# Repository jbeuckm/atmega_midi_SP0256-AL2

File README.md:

Try this SYSEX Editor app: [https://midi-tts.herokuapp.com/editor/index.html](https://midi-tts.herokuapp.com/editor/index.html)

Accepts MIDI signals to control a speech synthesizer IC. LTC6904 (on a DIP adapter) controls the clock frequency of the SP chip.

## MIDI Sysex Messages

Function   | Start | Prefix       | Message | End
-----------|-------|--------------|---------|-------
Set Channel| F0    | 77 34 01 00  | cc | f7
Speak Word | F0    | 77 34 01 01  | a1 a2 a3 ... (allophones) | f7
Assign Note On Word | F0    | 77 34 01 02 | nn (note #) a1 a2 a3 ... (allophones) | f7
Assign Note Off Word| F0    | 77 34 01 03 | nn (note #) a1 a2 a3 ... (allophones) | f7
Clock Freq | F0    | 77 34 01 40  | 0\[bits 13-7\] 0\[bits 6-0\] (khz) | f7
Save Config| F0    | 77 34 01 70  | (none) | f7
Load Config| F0    | 77 34 01 71  | (none) | f7
Dump Request| F0    | 77 34 01 72  | (none) | f7
Sysex Dump | F0    | 77 34 01 73  | (assignment data) | f7

After words have been assigned to keys, the device operates as a monophonic synthesizer, playing the word assigned to a key when that key is pressed.

If a "speak word" message is received while a key is down, the word is assigned to that key.

MIDI notes on the base channel trigger words that have been assigned to those keys.

MIDI notes on the base channel + 1 set the pitch by altering the clock frequency of the speech chip.

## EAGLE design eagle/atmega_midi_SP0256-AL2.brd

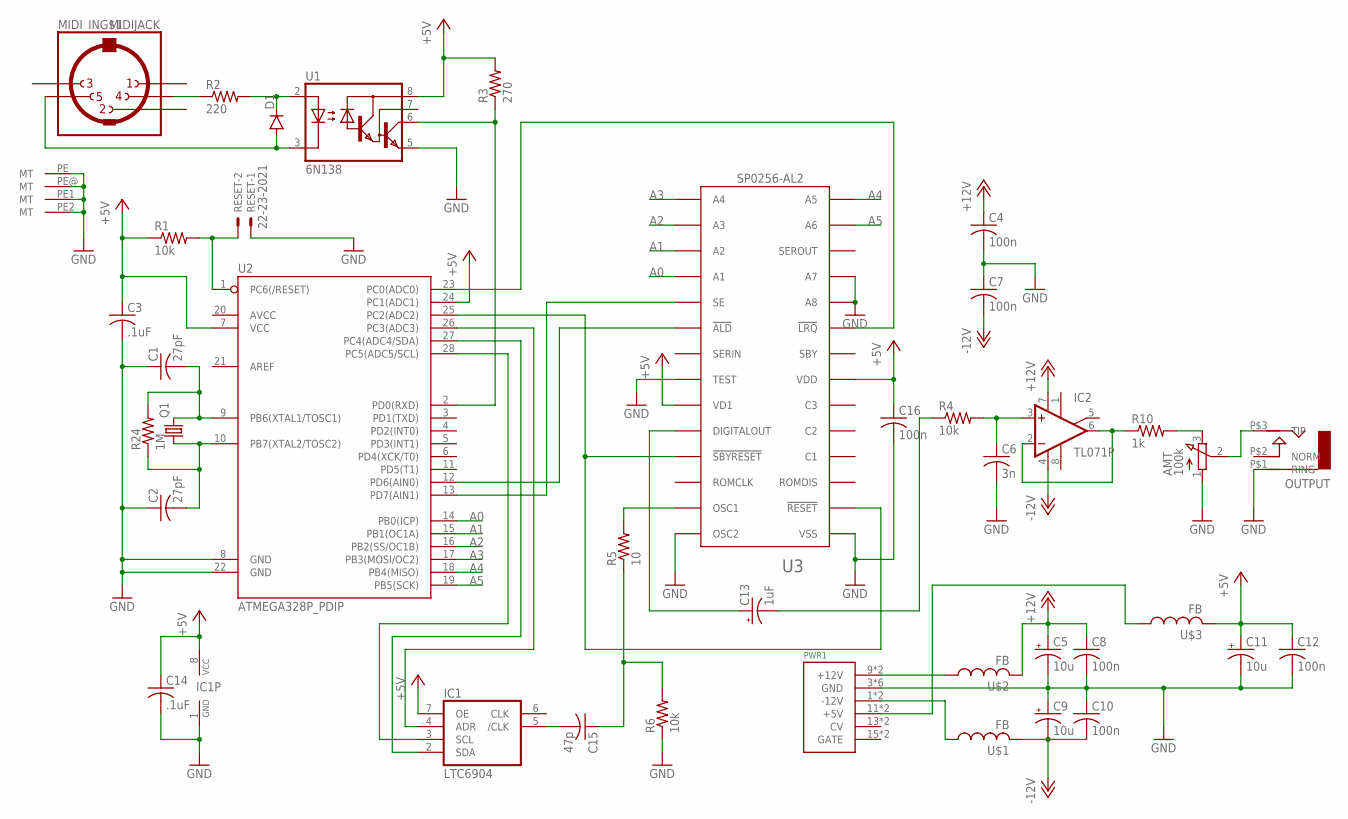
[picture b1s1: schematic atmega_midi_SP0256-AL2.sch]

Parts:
AMT: 100k; 3RP/1610N
C1, C2: 27pF; C025-040X050
C3, C14: .1uF; C025-030X050
C4: 100n; C050-024X044
C5, C9, C11: 10u; B45181A
C6: 3n; C050-024X044
C7, C8, C10, C12, C16: 100n; C025-030X050
C13: 1uF; E15-6
C15: 47p; C050-024X044
D1: DIODE1N4148; DIODE-1N4148
IC1: LTC6904; DIL08
IC2: TL071P; DIL08
MIDI_IN: MIDIJACK; CP-2350
OUTPUT: AUDIO-JACK; ERTHENVAR-JACK-90DEG
PWR1: POWER; POWER_16
Q1: CRYSTALHC49S; HC49/S
R1, R4, R6: 10k; 0207/7
R2: 220; 0207/7
R3: 270; 0207/7
R5: 10; 0207/7
R10: 1k; 0207/7
R24: 1M; 0207/7
RESET: 22-23-2021
U1: 6N138; DIL08
U2: ATMEGA328P_PDIP; DIL28-3
U3: SP0256-AL2; DIL28-6
U$1, U$2, U$3: FB

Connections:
+5V: C3.1, C11.+, C12.1, C14.1, C16.1, IC1.7 (OE), IC1.8 (VCC), R1.1, R3.2, U1.8 (VCC), U2.7 (VCC), U2.24 (PC1(ADC1)), U3.P$7 (VDD), U3.P$23 (VD1), U$3.P$2 (2)
+12V: C4.1, C5.+, C8.1, IC2.7 (V+), U$2.P$2 (2)
-12V: C7.2, C9.-, C10.2, IC2.4 (V-), U$1.P$2 (2)
A0: U2.14 (PB0(ICP)), U3.P$18 (A1)
A1: U2.15 (PB1(OC1A)), U3.P$17 (A2)
A2: U2.16 (PB2(SS/OC1B)), U3.P$16 (A3)
A3: U2.17 (PB3(MOSI/OC2)), U3.P$15 (A4)
A4: U2.18 (PB4(MISO)), U3.P$14 (A5)
A5: U2.19 (PB5(SCK)), U3.P$13 (A6)
GND: AMT.1 (A), C1.1, C2.1, C3.2, C4.2, C5.-, C6.2, C7.1, C8.2, C9.+, C10.1, C11.-, C12.2, C14.2, C16.2, IC1.1 (GND), MIDI_IN.PE (MT), MIDI_IN.PE1 (MT), MIDI_IN.PE2 (MT), MIDI_IN.PE@ (MT), OUTPUT.P$1 (RING), PWR1.3 (GND), PWR1.4 (GND), PWR1.5 (GND), PWR1.6 (GND), PWR1.7 (GND), PWR1.8 (GND), R6.1, RESET.1, U1.5 (GND), U2.8 (GND), U2.22 (GND), U3.P$1 (VSS), U3.P$10 (A8), U3.P$11 (A7), U3.P$22 (TEST), U3.P$28 (OSC2)
unnamed: U2.25 (PC2(ADC2)), U3.P$2 (!RESET), U3.P$25 (!SBYRESET)
unnamed: PWR1.11 (+5V), PWR1.12 (+5V), U$3.P$1 (1)
unnamed: D1.A, MIDI_IN.5, U1.3 (C)
unnamed: C1.2, Q1.2, R24.2, U2.9 (PB6(XTAL1/TOSC1))
unnamed: C2.2, Q1.1, R24.1, U2.10 (PB7(XTAL2/TOSC2))
unnamed: C6.1, IC2.3 (+IN), R4.2
unnamed: D1.C, R2.2, U1.2 (A)
unnamed: MIDI_IN.4, R2.1
unnamed: AMT.3 (E), R10.2
unnamed: U2.12 (PD6(AIN0)), U3.P$20 (!ALD)
unnamed: PWR1.9 (+12V), PWR1.10 (+12V), U$2.P$1 (1)
unnamed: IC2.2 (-IN), IC2.6 (OUT), R10.1
unnamed: AMT.2 (S), OUTPUT.P$3 (TIP)
unnamed: PWR1.1 (-12V), PWR1.2 (-12V), U$1.P$1 (1)
unnamed: IC1.3 (SCL), U2.28 (PC5(ADC5/SCL))
unnamed: U2.13 (PD7(AIN1)), U3.P$19 (SE)
unnamed: C13.+, U3.P$24 (DIGITALOUT)
unnamed: IC1.2 (SDA), U2.27 (PC4(ADC4/SDA))
unnamed: IC1.4 (ADR), U2.26 (PC3(ADC3))
unnamed: U2.23 (PC0(ADC0)), U3.P$9 (!LRQ)
unnamed: C15.2, IC1.5 (/CLK)
unnamed: R3.1, U1.6 (VO), U2.2 (PD0(RXD))
unnamed: C13.-, R4.1
unnamed: R5.2, U3.P$27 (OSC1)
unnamed: C15.1, R5.1, R6.2
unnamed: R1.2, RESET.2, U2.1 (PC6(/RESET))

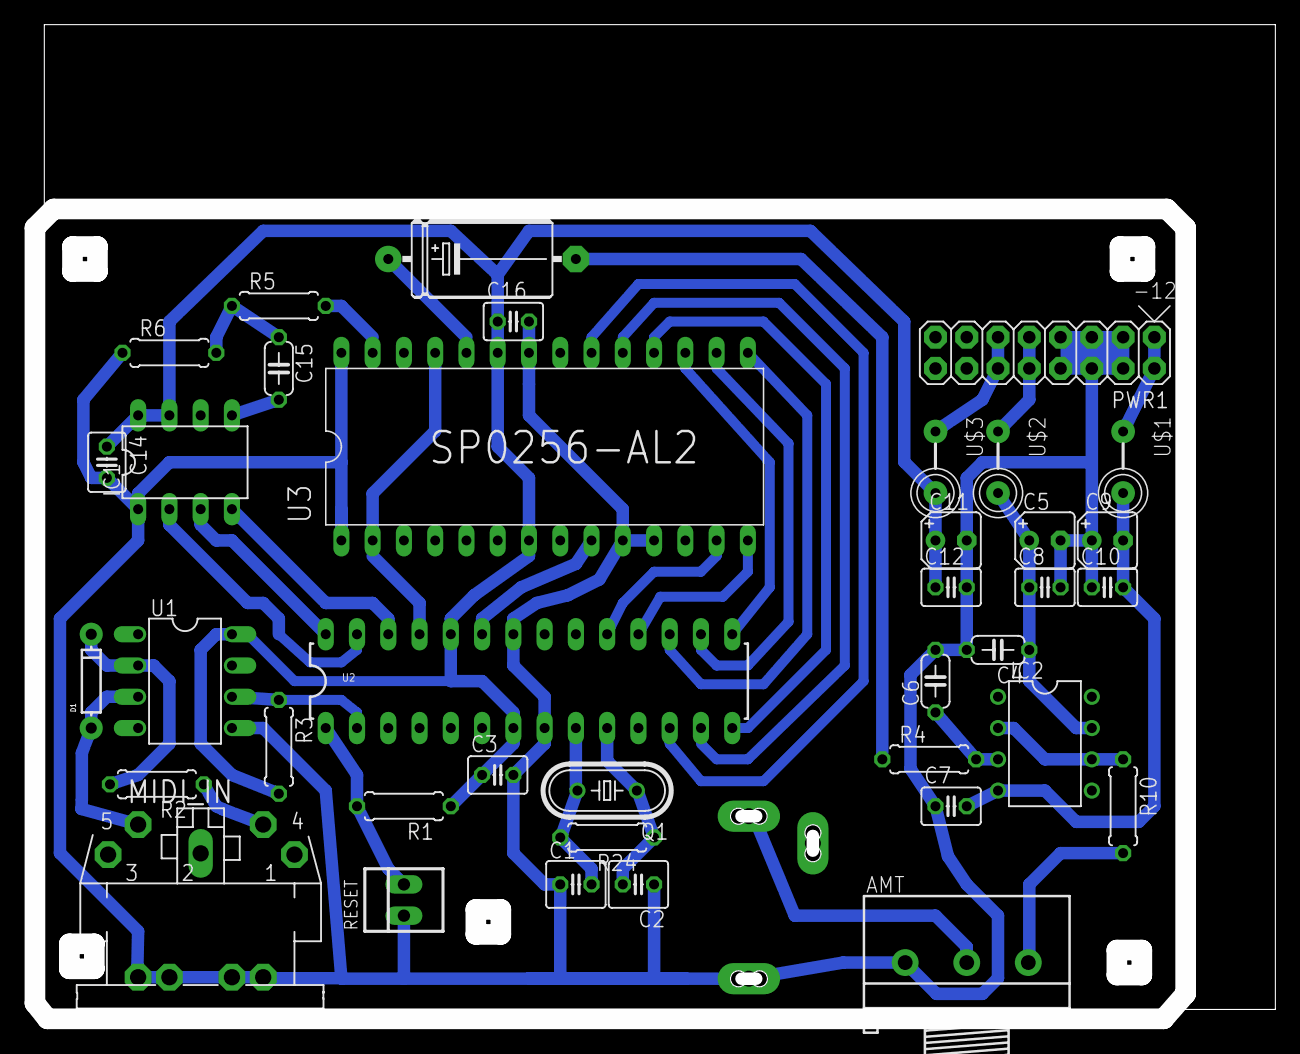
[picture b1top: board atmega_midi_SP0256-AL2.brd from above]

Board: 2 copper layers, 99.9 x 79.9 mm, 39 parts (0 on the bottom side), 36 nets.

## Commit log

2016-09-14 mostly there with sp chip
2016-09-15 parts on board
2016-09-15 layout adjusting
2016-09-15 93pct auto
2016-09-15 routed
2016-09-15 first cut
2016-09-15 starting a library for controlling the sp chip
2016-09-15 working up software
2016-09-15 arduino compiles
2016-09-16 compiles with calls to SP0256
2016-09-20 gate led working but no speech yet
2016-09-20 word constant defined
2016-09-20 purple has been spoken
2016-09-20 sysex speak function works
2016-09-20 schematic corrected for reset control
2016-09-20 board corrected for reset control
2016-09-21 adding allophone list class
2016-09-21 reset at beginning of each speakList()
2016-09-21 assign sysex speak word to current note
2016-09-21 save and load eeprom default config
2016-09-21 gate led while sysex speak word
2016-09-26 sysex doc
2016-10-01 new layout image
2016-11-26 panel and working cut
2016-11-26 added ltc6904
2016-11-26 renamed arduino code file and new board taking shape
2016-11-26 routed and stub code for pitch oscillator
2016-11-27 LTC interface and no gate led or out
2016-11-27 copied in frequencyKhz code
2016-11-27 readme
2016-11-27 new layout
2016-11-27 sysex to set clock freq
2016-11-27 refactoring for note off assignments
2016-11-27 listening for baseChannel + 1 to set pitch
2016-11-27 midi off right now

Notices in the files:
parts and their libraries:
SparkFun-DiscreteSemi: Licensing: Creative Commons ShareAlike 4.0 International - https://creativecommons.org/licenses/by-sa/4.0
